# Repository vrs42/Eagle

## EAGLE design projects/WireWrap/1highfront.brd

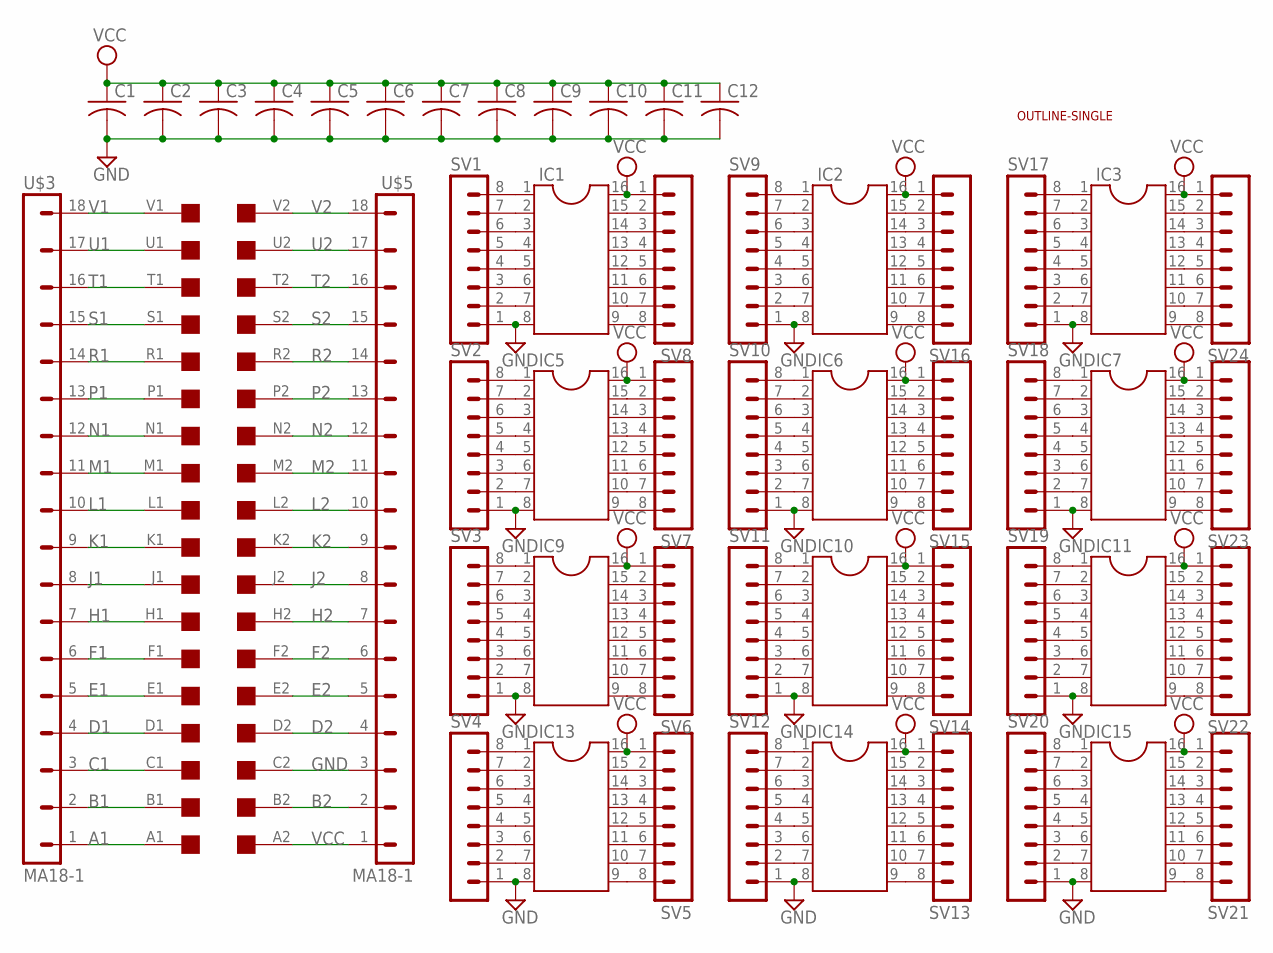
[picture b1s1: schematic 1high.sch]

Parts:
C1, C2, C3, C4, C5, C6, C7, C8, C9, C10, C11, C12: C-US050-025X075; C050-025X075
IC1, IC2, IC3, IC5, IC6, IC7, IC9, IC10, IC11, IC13, IC14, IC15: DIL16
SV1, SV2, SV3, SV4, SV5, SV6, SV7, SV8, SV9, SV10, SV11, SV12, SV13, SV14, SV15, SV16, SV17, SV18, SV19, SV20, SV21, SV22, SV23, SV24: MA08-1
U$2: OUTLINE-SINGLE; SINGLE
U$3, U$5: MA18-1
U$4: EDGE-2CONNECTOR; EDGE-CON2

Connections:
A1: U$3.1, U$4.A1
B1: U$3.2, U$4.B1
B2: U$4.B2, U$5.2
C1: U$3.3, U$4.C1
D1: U$3.4, U$4.D1
D2: U$4.D2, U$5.4
E1: U$3.5, U$4.E1
E2: U$4.E2, U$5.5
F1: U$3.6, U$4.F1
F2: U$4.F2, U$5.6
GND: C1.2, C2.2, C3.2, C4.2, C5.2, C6.2, C7.2, C8.2, C9.2, C10.2, C11.2, C12.2, IC1.8, IC2.8, IC3.8, IC5.8, IC6.8, IC7.8, IC9.8, IC10.8, IC11.8, IC13.8, IC14.8, IC15.8, SV1.1, SV2.1, SV3.1, SV4.1, SV9.1, SV10.1, SV11.1, SV12.1, SV17.1, SV18.1, SV19.1, SV20.1, U$4.C2, U$5.3
H1: U$3.7, U$4.H1
H2: U$4.H2, U$5.7
J1: U$3.8, U$4.J1
J2: U$4.J2, U$5.8
K1: U$3.9, U$4.K1
K2: U$4.K2, U$5.9
L1: U$3.10, U$4.L1
L2: U$4.L2, U$5.10
M1: U$3.11, U$4.M1
M2: U$4.M2, U$5.11
N1: U$3.12, U$4.N1
N2: U$4.N2, U$5.12
unnamed: IC1.7, SV1.2
unnamed: IC1.6, SV1.3
unnamed: IC1.5, SV1.4
unnamed: IC1.4, SV1.5
unnamed: IC1.3, SV1.6
unnamed: IC1.2, SV1.7
unnamed: IC1.1, SV1.8
unnamed: IC5.7, SV2.2
unnamed: IC5.6, SV2.3
unnamed: IC5.5, SV2.4
unnamed: IC5.4, SV2.5
unnamed: IC5.3, SV2.6
unnamed: IC5.2, SV2.7
unnamed: IC5.1, SV2.8
unnamed: IC9.7, SV3.2
unnamed: IC9.6, SV3.3
unnamed: IC9.5, SV3.4
unnamed: IC9.4, SV3.5
unnamed: IC9.3, SV3.6
unnamed: IC9.2, SV3.7
unnamed: IC9.1, SV3.8
unnamed: IC13.7, SV4.2
unnamed: IC13.6, SV4.3
unnamed: IC13.5, SV4.4
unnamed: IC13.4, SV4.5
unnamed: IC13.3, SV4.6
unnamed: IC13.2, SV4.7
unnamed: IC13.1, SV4.8
unnamed: IC2.1, SV9.8
unnamed: IC2.2, SV9.7
unnamed: IC2.3, SV9.6
unnamed: IC2.4, SV9.5
unnamed: IC2.5, SV9.4
unnamed: IC2.6, SV9.3
unnamed: IC2.7, SV9.2
unnamed: IC6.1, SV10.8
unnamed: IC6.2, SV10.7
unnamed: IC6.3, SV10.6
unnamed: IC6.4, SV10.5
unnamed: IC6.5, SV10.4
unnamed: IC6.6, SV10.3
unnamed: IC6.7, SV10.2
unnamed: IC10.1, SV11.8
unnamed: IC10.2, SV11.7
unnamed: IC10.3, SV11.6
unnamed: IC10.4, SV11.5
unnamed: IC10.5, SV11.4
unnamed: IC10.6, SV11.3
unnamed: IC10.7, SV11.2
unnamed: IC14.1, SV12.8
unnamed: IC14.2, SV12.7
unnamed: IC14.3, SV12.6
unnamed: IC14.4, SV12.5
unnamed: IC14.5, SV12.4
unnamed: IC14.6, SV12.3
unnamed: IC14.7, SV12.2
unnamed: IC6.15, SV15.2
unnamed: IC6.14, SV15.3
unnamed: IC6.13, SV15.4
unnamed: IC6.12, SV15.5
unnamed: IC6.11, SV15.6
unnamed: IC6.10, SV15.7
unnamed: IC6.9, SV15.8
unnamed: IC10.15, SV14.2
unnamed: IC10.14, SV14.3
unnamed: IC10.13, SV14.4
unnamed: IC10.12, SV14.5
unnamed: IC10.11, SV14.6
unnamed: IC10.10, SV14.7
unnamed: IC10.9, SV14.8
unnamed: IC1.9, SV8.8
unnamed: IC1.10, SV8.7
unnamed: IC1.11, SV8.6
unnamed: IC1.12, SV8.5
unnamed: IC1.13, SV8.4
unnamed: IC1.14, SV8.3
unnamed: IC1.15, SV8.2
unnamed: IC5.9, SV7.8
unnamed: IC5.10, SV7.7
unnamed: IC5.11, SV7.6
unnamed: IC5.12, SV7.5
unnamed: IC5.13, SV7.4
unnamed: IC5.14, SV7.3
unnamed: IC5.15, SV7.2
unnamed: IC2.15, SV16.2
unnamed: IC2.14, SV16.3
unnamed: IC2.13, SV16.4
unnamed: IC2.12, SV16.5
unnamed: IC2.11, SV16.6
unnamed: IC2.10, SV16.7
unnamed: IC2.9, SV16.8
unnamed: IC13.15, SV5.2
unnamed: IC13.14, SV5.3
unnamed: IC13.13, SV5.4
unnamed: IC13.12, SV5.5
unnamed: IC13.11, SV5.6
unnamed: IC13.10, SV5.7
unnamed: IC13.9, SV5.8
unnamed: IC9.15, SV6.2
unnamed: IC9.14, SV6.3
unnamed: IC9.13, SV6.4
unnamed: IC9.12, SV6.5
unnamed: IC9.11, SV6.6
unnamed: IC9.10, SV6.7
unnamed: IC9.9, SV6.8
unnamed: IC14.15, SV13.2
unnamed: IC14.14, SV13.3
unnamed: IC14.13, SV13.4
unnamed: IC14.12, SV13.5
unnamed: IC14.11, SV13.6
unnamed: IC14.10, SV13.7
unnamed: IC14.9, SV13.8
unnamed: IC3.7, SV17.2
unnamed: IC3.6, SV17.3
unnamed: IC3.5, SV17.4
unnamed: IC3.4, SV17.5
unnamed: IC3.3, SV17.6
unnamed: IC3.2, SV17.7
unnamed: IC3.1, SV17.8
unnamed: IC7.7, SV18.2
unnamed: IC7.6, SV18.3
unnamed: IC7.5, SV18.4
unnamed: IC7.4, SV18.5
unnamed: IC7.3, SV18.6
unnamed: IC7.2, SV18.7
unnamed: IC7.1, SV18.8
unnamed: IC11.7, SV19.2
unnamed: IC11.6, SV19.3
unnamed: IC11.5, SV19.4
unnamed: IC11.4, SV19.5
unnamed: IC11.3, SV19.6
unnamed: IC11.2, SV19.7
unnamed: IC11.1, SV19.8
unnamed: IC15.7, SV20.2
unnamed: IC15.6, SV20.3
unnamed: IC15.5, SV20.4
unnamed: IC15.4, SV20.5
unnamed: IC15.3, SV20.6
unnamed: IC15.2, SV20.7
unnamed: IC15.1, SV20.8
unnamed: IC15.15, SV21.2
unnamed: IC15.14, SV21.3
unnamed: IC15.13, SV21.4
unnamed: IC15.12, SV21.5
unnamed: IC15.11, SV21.6
unnamed: IC15.10, SV21.7
unnamed: IC15.9, SV21.8
unnamed: IC11.15, SV22.2
unnamed: IC11.14, SV22.3
unnamed: IC11.13, SV22.4
unnamed: IC11.12, SV22.5
unnamed: IC11.11, SV22.6
unnamed: IC11.10, SV22.7
unnamed: IC11.9, SV22.8
unnamed: IC7.15, SV23.2
unnamed: IC7.14, SV23.3
unnamed: IC7.13, SV23.4
unnamed: IC7.12, SV23.5
unnamed: IC7.11, SV23.6
unnamed: IC7.10, SV23.7
unnamed: IC7.9, SV23.8
unnamed: IC3.15, SV24.2
unnamed: IC3.14, SV24.3
unnamed: IC3.13, SV24.4
unnamed: IC3.12, SV24.5
unnamed: IC3.11, SV24.6
unnamed: IC3.10, SV24.7
unnamed: IC3.9, SV24.8
P1: U$3.13, U$4.P1
P2: U$4.P2, U$5.13
R1: U$3.14, U$4.R1
R2: U$4.R2, U$5.14
S1: U$3.15, U$4.S1
S2: U$4.S2, U$5.15
T1: U$3.16, U$4.T1
T2: U$4.T2, U$5.16
U1: U$3.17, U$4.U1
U2: U$4.U2, U$5.17
V1: U$3.18, U$4.V1
V2: U$4.V2, U$5.18
VCC: C1.1, C2.1, C3.1, C4.1, C5.1, C6.1, C7.1, C8.1, C9.1, C10.1, C11.1, C12.1, IC1.16, IC2.16, IC3.16, IC5.16, IC6.16, IC7.16, IC9.16, IC10.16, IC11.16, IC13.16, IC14.16, IC15.16, SV5.1, SV6.1, SV7.1, SV8.1, SV13.1, SV14.1, SV15.1, SV16.1, SV21.1, SV22.1, SV23.1, SV24.1, U$4.A2, U$5.1

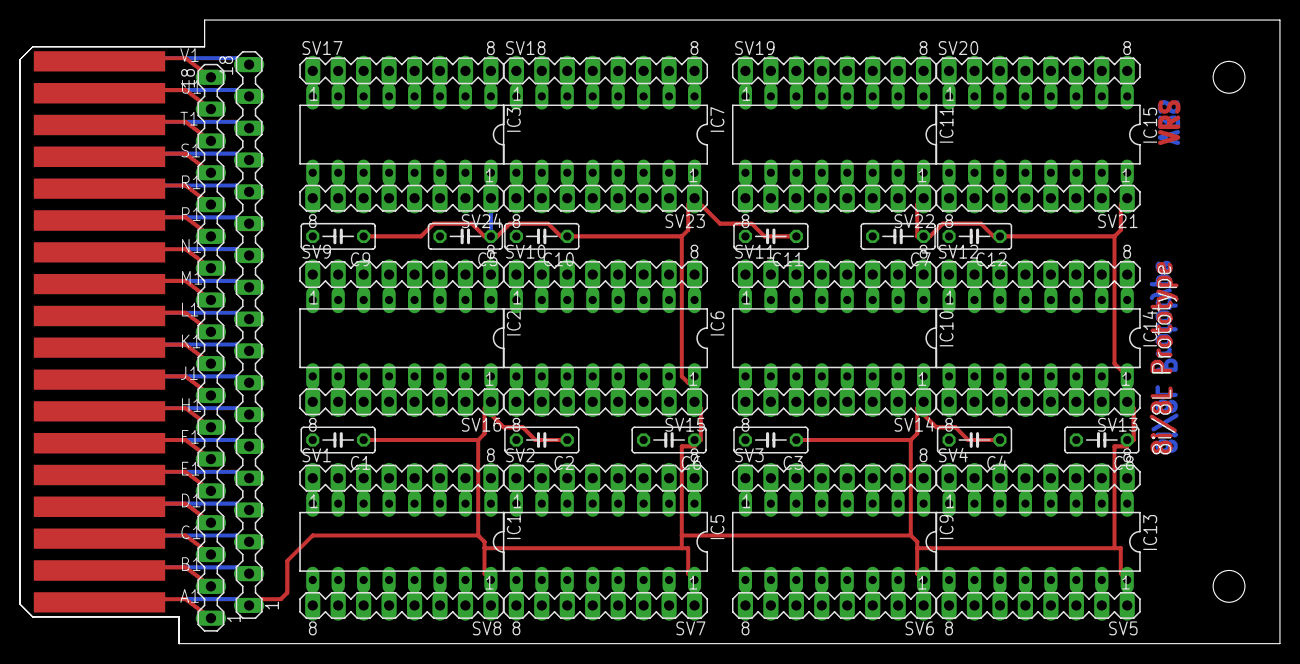
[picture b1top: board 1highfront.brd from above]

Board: 2 copper layers, 125.7 x 62.2 mm, 52 parts (0 on the bottom side), 204 nets.

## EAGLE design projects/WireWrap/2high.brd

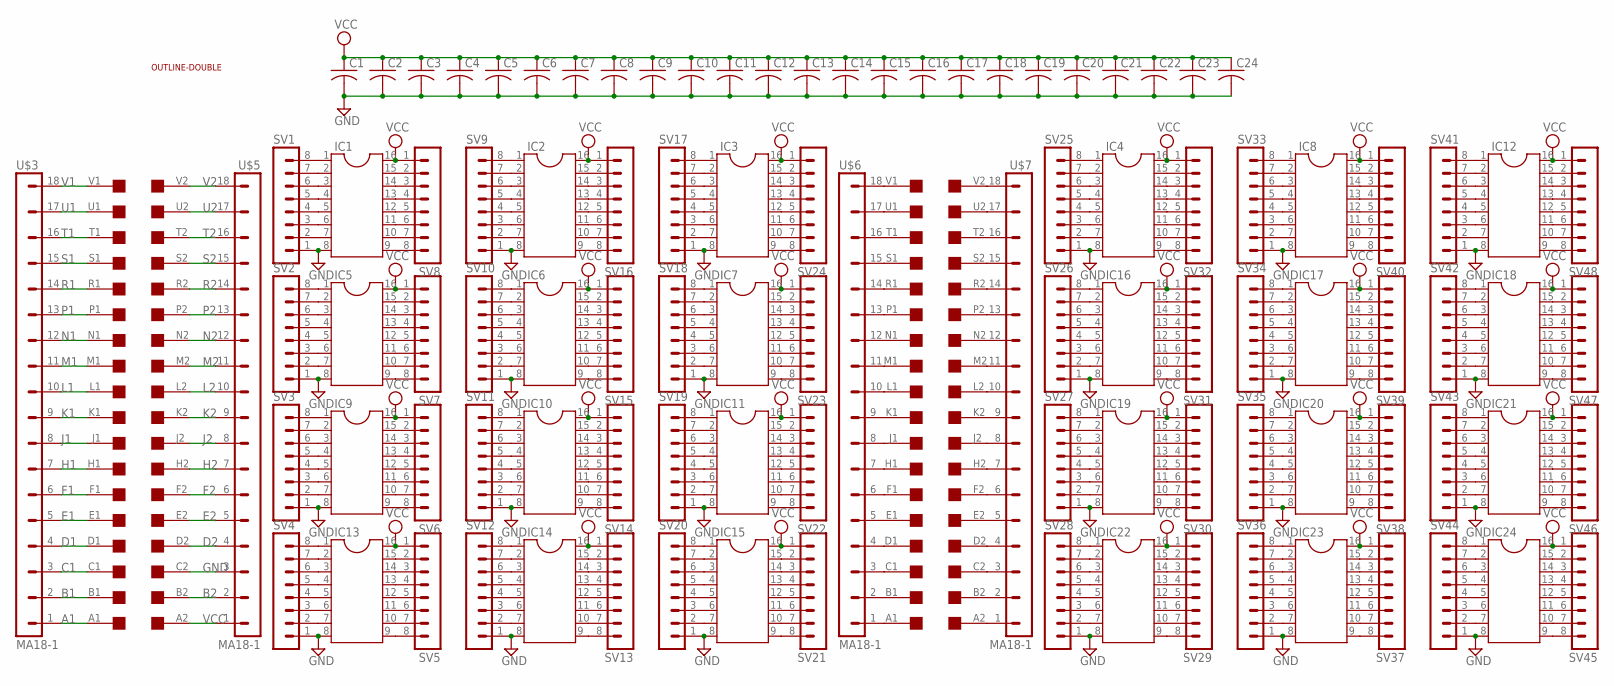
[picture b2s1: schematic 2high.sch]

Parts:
C1, C2, C3, C4, C5, C6, C7, C8, C9, C10, C11, C12, C13, C14, C15, C16, C17, C18, C19, C20, C21, C22, C23, C24: C-US050-025X075; C050-025X075
IC1, IC2, IC3, IC4, IC5, IC6, IC7, IC8, IC9, IC10, IC11, IC12, IC13, IC14, IC15, IC16, IC17, IC18, IC19, IC20, IC21, IC22, IC23, IC24: DIL16
SV1, SV2, SV3, SV4, SV5, SV6, SV7, SV8, SV9, SV10, SV11, SV12, SV13, SV14, SV15, SV16, SV17, SV18, SV19, SV20, SV21, SV22, SV23, SV24, SV25, SV26, SV27, SV28, SV29, SV30, SV31, SV32, SV33, SV34, SV35, SV36, SV37, SV38, SV39, SV40, SV41, SV42, SV43, SV44, SV45, SV46, SV47, SV48: MA08-1
U$1: OUTLINE-DOUBLE; DOUBLE
U$2, U$4: EDGE-2CONNECTOR; EDGE-CON2
U$3, U$5, U$6, U$7: MA18-1

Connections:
A1: U$3.1, U$4.A1
B1: U$3.2, U$4.B1
B2: U$4.B2, U$5.2
C1: U$3.3, U$4.C1
D1: U$3.4, U$4.D1
D2: U$4.D2, U$5.4
E1: U$3.5, U$4.E1
E2: U$4.E2, U$5.5
F1: U$3.6, U$4.F1
F2: U$4.F2, U$5.6
GND: C1.2, C2.2, C3.2, C4.2, C5.2, C6.2, C7.2, C8.2, C9.2, C10.2, C11.2, C12.2, C13.2, C14.2, C15.2, C16.2, C17.2, C18.2, C19.2, C20.2, C21.2, C22.2, C23.2, C24.2, IC1.8, IC2.8, IC3.8, IC4.8, IC5.8, IC6.8, IC7.8, IC8.8, IC9.8, IC10.8, IC11.8, IC12.8, IC13.8, IC14.8, IC15.8, IC16.8, IC17.8, IC18.8, IC19.8, IC20.8, IC21.8, IC22.8, IC23.8, IC24.8, SV1.1, SV2.1, SV3.1, SV4.1, SV9.1, SV10.1, SV11.1, SV12.1, SV17.1, SV18.1, SV19.1, SV20.1, SV25.1, SV26.1, SV27.1, SV28.1, SV33.1, SV34.1, SV35.1, SV36.1, SV41.1, SV42.1, SV43.1, SV44.1, U$4.C2, U$5.3
H1: U$3.7, U$4.H1
H2: U$4.H2, U$5.7
J1: U$3.8, U$4.J1
J2: U$4.J2, U$5.8
K1: U$3.9, U$4.K1
K2: U$4.K2, U$5.9
L1: U$3.10, U$4.L1
L2: U$4.L2, U$5.10
M1: U$3.11, U$4.M1
M2: U$4.M2, U$5.11
N1: U$3.12, U$4.N1
N2: U$4.N2, U$5.12
unnamed: IC1.7, SV1.2
unnamed: IC1.6, SV1.3
unnamed: IC1.5, SV1.4
unnamed: IC1.4, SV1.5
unnamed: IC1.3, SV1.6
unnamed: IC1.2, SV1.7
unnamed: IC1.1, SV1.8
unnamed: IC5.7, SV2.2
unnamed: IC5.6, SV2.3
unnamed: IC5.5, SV2.4
unnamed: IC5.4, SV2.5
unnamed: IC5.3, SV2.6
unnamed: IC5.2, SV2.7
unnamed: IC5.1, SV2.8
unnamed: IC9.7, SV3.2
unnamed: IC9.6, SV3.3
unnamed: IC9.5, SV3.4
unnamed: IC9.4, SV3.5
unnamed: IC9.3, SV3.6
unnamed: IC9.2, SV3.7
unnamed: IC9.1, SV3.8
unnamed: IC13.7, SV4.2
unnamed: IC13.6, SV4.3
unnamed: IC13.5, SV4.4
unnamed: IC13.4, SV4.5
unnamed: IC13.3, SV4.6
unnamed: IC13.2, SV4.7
unnamed: IC13.1, SV4.8
unnamed: IC2.1, SV9.8
unnamed: IC2.2, SV9.7
unnamed: IC2.3, SV9.6
unnamed: IC2.4, SV9.5
unnamed: IC2.5, SV9.4
unnamed: IC2.6, SV9.3
unnamed: IC2.7, SV9.2
unnamed: IC6.1, SV10.8
unnamed: IC6.2, SV10.7
unnamed: IC6.3, SV10.6
unnamed: IC6.4, SV10.5
unnamed: IC6.5, SV10.4
unnamed: IC6.6, SV10.3
unnamed: IC6.7, SV10.2
unnamed: IC10.1, SV11.8
unnamed: IC10.2, SV11.7
unnamed: IC10.3, SV11.6
unnamed: IC10.4, SV11.5
unnamed: IC10.5, SV11.4
unnamed: IC10.6, SV11.3
unnamed: IC10.7, SV11.2
unnamed: IC14.1, SV12.8
unnamed: IC14.2, SV12.7
unnamed: IC14.3, SV12.6
unnamed: IC14.4, SV12.5
unnamed: IC14.5, SV12.4
unnamed: IC14.6, SV12.3
unnamed: IC14.7, SV12.2
unnamed: IC6.15, SV15.2
unnamed: IC6.14, SV15.3
unnamed: IC6.13, SV15.4
unnamed: IC6.12, SV15.5
unnamed: IC6.11, SV15.6
unnamed: IC6.10, SV15.7
unnamed: IC6.9, SV15.8
unnamed: IC10.15, SV14.2
unnamed: IC10.14, SV14.3
unnamed: IC10.13, SV14.4
unnamed: IC10.12, SV14.5
unnamed: IC10.11, SV14.6
unnamed: IC10.10, SV14.7
unnamed: IC10.9, SV14.8
unnamed: IC1.9, SV8.8
unnamed: IC1.10, SV8.7
unnamed: IC1.11, SV8.6
unnamed: IC1.12, SV8.5
unnamed: IC1.13, SV8.4
unnamed: IC1.14, SV8.3
unnamed: IC1.15, SV8.2
unnamed: IC5.9, SV7.8
unnamed: IC5.10, SV7.7
unnamed: IC5.11, SV7.6
unnamed: IC5.12, SV7.5
unnamed: IC5.13, SV7.4
unnamed: IC5.14, SV7.3
unnamed: IC5.15, SV7.2
unnamed: IC2.15, SV16.2
unnamed: IC2.14, SV16.3
unnamed: IC2.13, SV16.4
unnamed: IC2.12, SV16.5
unnamed: IC2.11, SV16.6
unnamed: IC2.10, SV16.7
unnamed: IC2.9, SV16.8
unnamed: IC13.15, SV5.2
unnamed: IC13.14, SV5.3
unnamed: IC13.13, SV5.4
unnamed: IC13.12, SV5.5
unnamed: IC13.11, SV5.6
unnamed: IC13.10, SV5.7
unnamed: IC13.9, SV5.8
unnamed: IC9.15, SV6.2
unnamed: IC9.14, SV6.3
unnamed: IC9.13, SV6.4
unnamed: IC9.12, SV6.5
unnamed: IC9.11, SV6.6
unnamed: IC9.10, SV6.7
unnamed: IC9.9, SV6.8
unnamed: IC14.15, SV13.2
unnamed: IC14.14, SV13.3
unnamed: IC14.13, SV13.4
unnamed: IC14.12, SV13.5
unnamed: IC14.11, SV13.6
unnamed: IC14.10, SV13.7
unnamed: IC14.9, SV13.8
unnamed: IC3.7, SV17.2
unnamed: IC3.6, SV17.3
unnamed: IC3.5, SV17.4
unnamed: IC3.4, SV17.5
unnamed: IC3.3, SV17.6
unnamed: IC3.2, SV17.7
unnamed: IC3.1, SV17.8
unnamed: IC7.7, SV18.2
unnamed: IC7.6, SV18.3
unnamed: IC7.5, SV18.4
unnamed: IC7.4, SV18.5
unnamed: IC7.3, SV18.6
unnamed: IC7.2, SV18.7
unnamed: IC7.1, SV18.8
unnamed: IC11.7, SV19.2
unnamed: IC11.6, SV19.3
unnamed: IC11.5, SV19.4
unnamed: IC11.4, SV19.5
unnamed: IC11.3, SV19.6
unnamed: IC11.2, SV19.7
unnamed: IC11.1, SV19.8
unnamed: IC15.7, SV20.2
unnamed: IC15.6, SV20.3
unnamed: IC15.5, SV20.4
unnamed: IC15.4, SV20.5
unnamed: IC15.3, SV20.6
unnamed: IC15.2, SV20.7
unnamed: IC15.1, SV20.8
unnamed: IC15.15, SV21.2
unnamed: IC15.14, SV21.3
unnamed: IC15.13, SV21.4
unnamed: IC15.12, SV21.5
unnamed: IC15.11, SV21.6
unnamed: IC15.10, SV21.7
unnamed: IC15.9, SV21.8
unnamed: IC11.15, SV22.2
unnamed: IC11.14, SV22.3
unnamed: IC11.13, SV22.4
unnamed: IC11.12, SV22.5
unnamed: IC11.11, SV22.6
unnamed: IC11.10, SV22.7
unnamed: IC11.9, SV22.8
unnamed: IC7.15, SV23.2
unnamed: IC7.14, SV23.3
unnamed: IC7.13, SV23.4
unnamed: IC7.12, SV23.5
unnamed: IC7.11, SV23.6
unnamed: IC7.10, SV23.7
unnamed: IC7.9, SV23.8
unnamed: IC3.15, SV24.2
unnamed: IC3.14, SV24.3
unnamed: IC3.13, SV24.4
unnamed: IC3.12, SV24.5
unnamed: IC3.11, SV24.6
unnamed: IC3.10, SV24.7
unnamed: IC3.9, SV24.8
unnamed: U$2.A2, U$7.1
unnamed: U$2.A1, U$6.1
unnamed: U$2.B1, U$6.2
unnamed: U$2.B2, U$7.2
unnamed: U$2.C2, U$7.3
unnamed: U$2.C1, U$6.3
unnamed: U$2.D1, U$6.4
unnamed: U$2.D2, U$7.4
unnamed: U$2.E2, U$7.5
unnamed: U$2.E1, U$6.5
unnamed: U$2.F1, U$6.6
unnamed: U$2.F2, U$7.6
unnamed: U$2.H2, U$7.7
unnamed: U$2.H1, U$6.7
unnamed: U$2.J1, U$6.8
unnamed: U$2.J2, U$7.8
unnamed: U$2.K2, U$7.9
unnamed: U$2.K1, U$6.9
unnamed: U$2.L1, U$6.10
unnamed: U$2.L2, U$7.10
unnamed: U$2.M2, U$7.11
unnamed: U$2.M1, U$6.11
unnamed: U$2.N1, U$6.12
unnamed: U$2.P1, U$6.13
unnamed: U$2.P2, U$7.13
unnamed: U$2.N2, U$7.12
unnamed: U$2.V1, U$6.18
unnamed: U$2.U1, U$6.17
unnamed: U$2.T1, U$6.16
unnamed: U$2.S1, U$6.15
unnamed: U$2.R1, U$6.14
unnamed: U$2.V2, U$7.18
unnamed: U$2.U2, U$7.17
unnamed: U$2.T2, U$7.16
unnamed: U$2.S2, U$7.15
unnamed: U$2.R2, U$7.14
unnamed: IC4.7, SV25.2
unnamed: IC4.6, SV25.3
unnamed: IC4.5, SV25.4
unnamed: IC4.4, SV25.5
unnamed: IC4.3, SV25.6
unnamed: IC4.2, SV25.7
unnamed: IC4.1, SV25.8
unnamed: IC16.7, SV26.2
unnamed: IC16.6, SV26.3
unnamed: IC16.5, SV26.4
unnamed: IC16.4, SV26.5
unnamed: IC16.3, SV26.6
unnamed: IC16.2, SV26.7
unnamed: IC16.1, SV26.8
unnamed: IC19.7, SV27.2
unnamed: IC19.6, SV27.3
unnamed: IC19.5, SV27.4
unnamed: IC19.4, SV27.5
unnamed: IC19.3, SV27.6
unnamed: IC19.2, SV27.7
unnamed: IC19.1, SV27.8
unnamed: IC22.7, SV28.2
unnamed: IC22.6, SV28.3
unnamed: IC22.5, SV28.4
unnamed: IC22.4, SV28.5
unnamed: IC22.3, SV28.6
unnamed: IC22.2, SV28.7
unnamed: IC22.1, SV28.8
unnamed: IC8.1, SV33.8
unnamed: IC8.2, SV33.7
unnamed: IC8.3, SV33.6
unnamed: IC8.4, SV33.5
unnamed: IC8.5, SV33.4
unnamed: IC8.6, SV33.3
unnamed: IC8.7, SV33.2
unnamed: IC17.1, SV34.8
unnamed: IC17.2, SV34.7
unnamed: IC17.3, SV34.6
unnamed: IC17.4, SV34.5
unnamed: IC17.5, SV34.4
unnamed: IC17.6, SV34.3
unnamed: IC17.7, SV34.2
unnamed: IC20.1, SV35.8
unnamed: IC20.2, SV35.7
unnamed: IC20.3, SV35.6
unnamed: IC20.4, SV35.5
unnamed: IC20.5, SV35.4
unnamed: IC20.6, SV35.3
unnamed: IC20.7, SV35.2
unnamed: IC23.1, SV36.8
unnamed: IC23.2, SV36.7
unnamed: IC23.3, SV36.6
unnamed: IC23.4, SV36.5
unnamed: IC23.5, SV36.4
unnamed: IC23.6, SV36.3
unnamed: IC23.7, SV36.2
unnamed: IC17.15, SV39.2
unnamed: IC17.14, SV39.3
unnamed: IC17.13, SV39.4
unnamed: IC17.12, SV39.5
unnamed: IC17.11, SV39.6
unnamed: IC17.10, SV39.7
unnamed: IC17.9, SV39.8
unnamed: IC20.15, SV38.2
unnamed: IC20.14, SV38.3
unnamed: IC20.13, SV38.4
unnamed: IC20.12, SV38.5
unnamed: IC20.11, SV38.6
unnamed: IC20.10, SV38.7
unnamed: IC20.9, SV38.8
unnamed: IC4.9, SV32.8
unnamed: IC4.10, SV32.7
unnamed: IC4.11, SV32.6
unnamed: IC4.12, SV32.5
unnamed: IC4.13, SV32.4
unnamed: IC4.14, SV32.3
unnamed: IC4.15, SV32.2
unnamed: IC16.9, SV31.8
unnamed: IC16.10, SV31.7
unnamed: IC16.11, SV31.6
unnamed: IC16.12, SV31.5
unnamed: IC16.13, SV31.4
unnamed: IC16.14, SV31.3
unnamed: IC16.15, SV31.2
unnamed: IC8.15, SV40.2
unnamed: IC8.14, SV40.3
unnamed: IC8.13, SV40.4
unnamed: IC8.12, SV40.5
unnamed: IC8.11, SV40.6
unnamed: IC8.10, SV40.7
unnamed: IC8.9, SV40.8
unnamed: IC22.15, SV29.2
unnamed: IC22.14, SV29.3
unnamed: IC22.13, SV29.4
unnamed: IC22.12, SV29.5
unnamed: IC22.11, SV29.6
unnamed: IC22.10, SV29.7
unnamed: IC22.9, SV29.8
unnamed: IC19.15, SV30.2
unnamed: IC19.14, SV30.3
unnamed: IC19.13, SV30.4
unnamed: IC19.12, SV30.5
unnamed: IC19.11, SV30.6
unnamed: IC19.10, SV30.7
unnamed: IC19.9, SV30.8
unnamed: IC23.15, SV37.2
unnamed: IC23.14, SV37.3
unnamed: IC23.13, SV37.4
unnamed: IC23.12, SV37.5
unnamed: IC23.11, SV37.6
unnamed: IC23.10, SV37.7
unnamed: IC23.9, SV37.8
unnamed: IC12.7, SV41.2
unnamed: IC12.6, SV41.3
unnamed: IC12.5, SV41.4
unnamed: IC12.4, SV41.5
unnamed: IC12.3, SV41.6
unnamed: IC12.2, SV41.7
unnamed: IC12.1, SV41.8
unnamed: IC18.7, SV42.2
unnamed: IC18.6, SV42.3
unnamed: IC18.5, SV42.4
unnamed: IC18.4, SV42.5
unnamed: IC18.3, SV42.6
unnamed: IC18.2, SV42.7
unnamed: IC18.1, SV42.8
unnamed: IC21.7, SV43.2
unnamed: IC21.6, SV43.3
unnamed: IC21.5, SV43.4
unnamed: IC21.4, SV43.5
unnamed: IC21.3, SV43.6
unnamed: IC21.2, SV43.7
unnamed: IC21.1, SV43.8
unnamed: IC24.7, SV44.2
unnamed: IC24.6, SV44.3
unnamed: IC24.5, SV44.4
unnamed: IC24.4, SV44.5
unnamed: IC24.3, SV44.6
unnamed: IC24.2, SV44.7
unnamed: IC24.1, SV44.8
unnamed: IC24.15, SV45.2
unnamed: IC24.14, SV45.3
unnamed: IC24.13, SV45.4
unnamed: IC24.12, SV45.5
unnamed: IC24.11, SV45.6
unnamed: IC24.10, SV45.7
unnamed: IC24.9, SV45.8
unnamed: IC21.15, SV46.2
unnamed: IC21.14, SV46.3
unnamed: IC21.13, SV46.4
unnamed: IC21.12, SV46.5
unnamed: IC21.11, SV46.6
unnamed: IC21.10, SV46.7
unnamed: IC21.9, SV46.8
unnamed: IC18.15, SV47.2
unnamed: IC18.14, SV47.3
unnamed: IC18.13, SV47.4
unnamed: IC18.12, SV47.5
unnamed: IC18.11, SV47.6
unnamed: IC18.10, SV47.7
unnamed: IC18.9, SV47.8
unnamed: IC12.15, SV48.2
unnamed: IC12.14, SV48.3
unnamed: IC12.13, SV48.4
unnamed: IC12.12, SV48.5
unnamed: IC12.11, SV48.6
unnamed: IC12.10, SV48.7
unnamed: IC12.9, SV48.8
P1: U$3.13, U$4.P1
P2: U$4.P2, U$5.13
R1: U$3.14, U$4.R1
R2: U$4.R2, U$5.14
S1: U$3.15, U$4.S1
S2: U$4.S2, U$5.15
T1: U$3.16, U$4.T1
T2: U$4.T2, U$5.16
U1: U$3.17, U$4.U1
U2: U$4.U2, U$5.17
V1: U$3.18, U$4.V1
V2: U$4.V2, U$5.18
VCC: C1.1, C2.1, C3.1, C4.1, C5.1, C6.1, C7.1, C8.1, C9.1, C10.1, C11.1, C12.1, C13.1, C14.1, C15.1, C16.1, C17.1, C18.1, C19.1, C20.1, C21.1, C22.1, C23.1, C24.1, IC1.16, IC2.16, IC3.16, IC4.16, IC5.16, IC6.16, IC7.16, IC8.16, IC9.16, IC10.16, IC11.16, IC12.16, IC13.16, IC14.16, IC15.16, IC16.16, IC17.16, IC18.16, IC19.16, IC20.16, IC21.16, IC22.16, IC23.16, IC24.16, SV5.1, SV6.1, SV7.1, SV8.1, SV13.1, SV14.1, SV15.1, SV16.1, SV21.1, SV22.1, SV23.1, SV24.1, SV29.1, SV30.1, SV31.1, SV32.1, SV37.1, SV38.1, SV39.1, SV40.1, SV45.1, SV46.1, SV47.1, SV48.1, U$4.A2, U$5.1

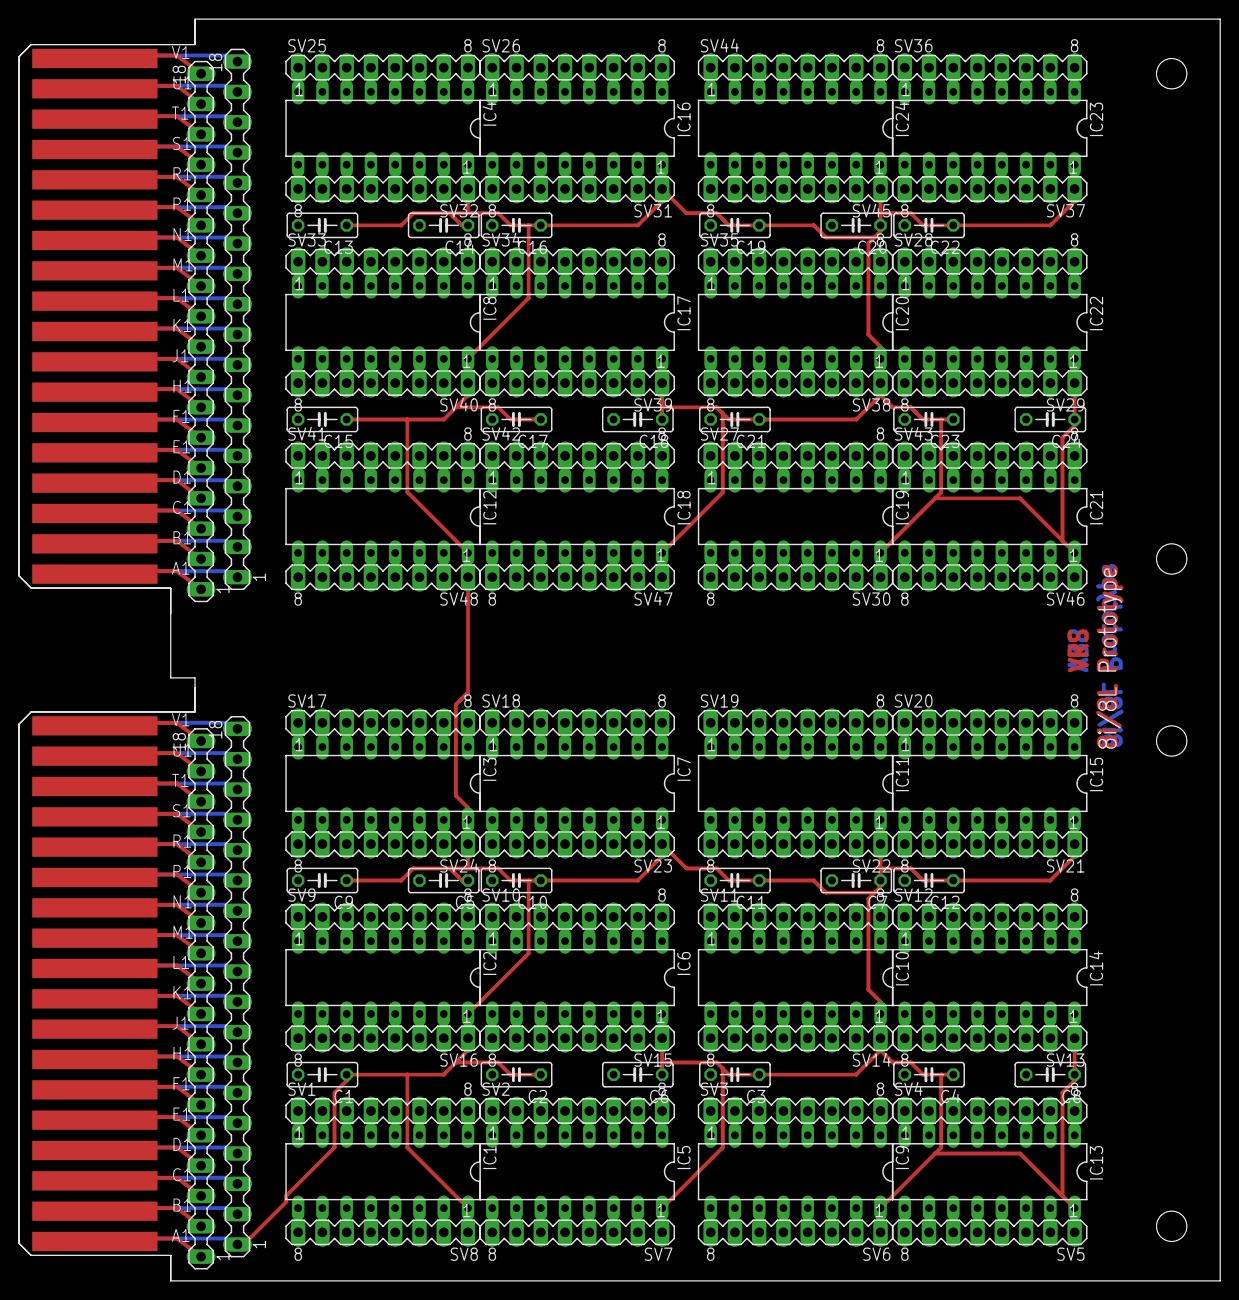
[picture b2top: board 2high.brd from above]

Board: 2 copper layers, 125.7 x 132.1 mm, 103 parts (0 on the bottom side), 408 nets.
